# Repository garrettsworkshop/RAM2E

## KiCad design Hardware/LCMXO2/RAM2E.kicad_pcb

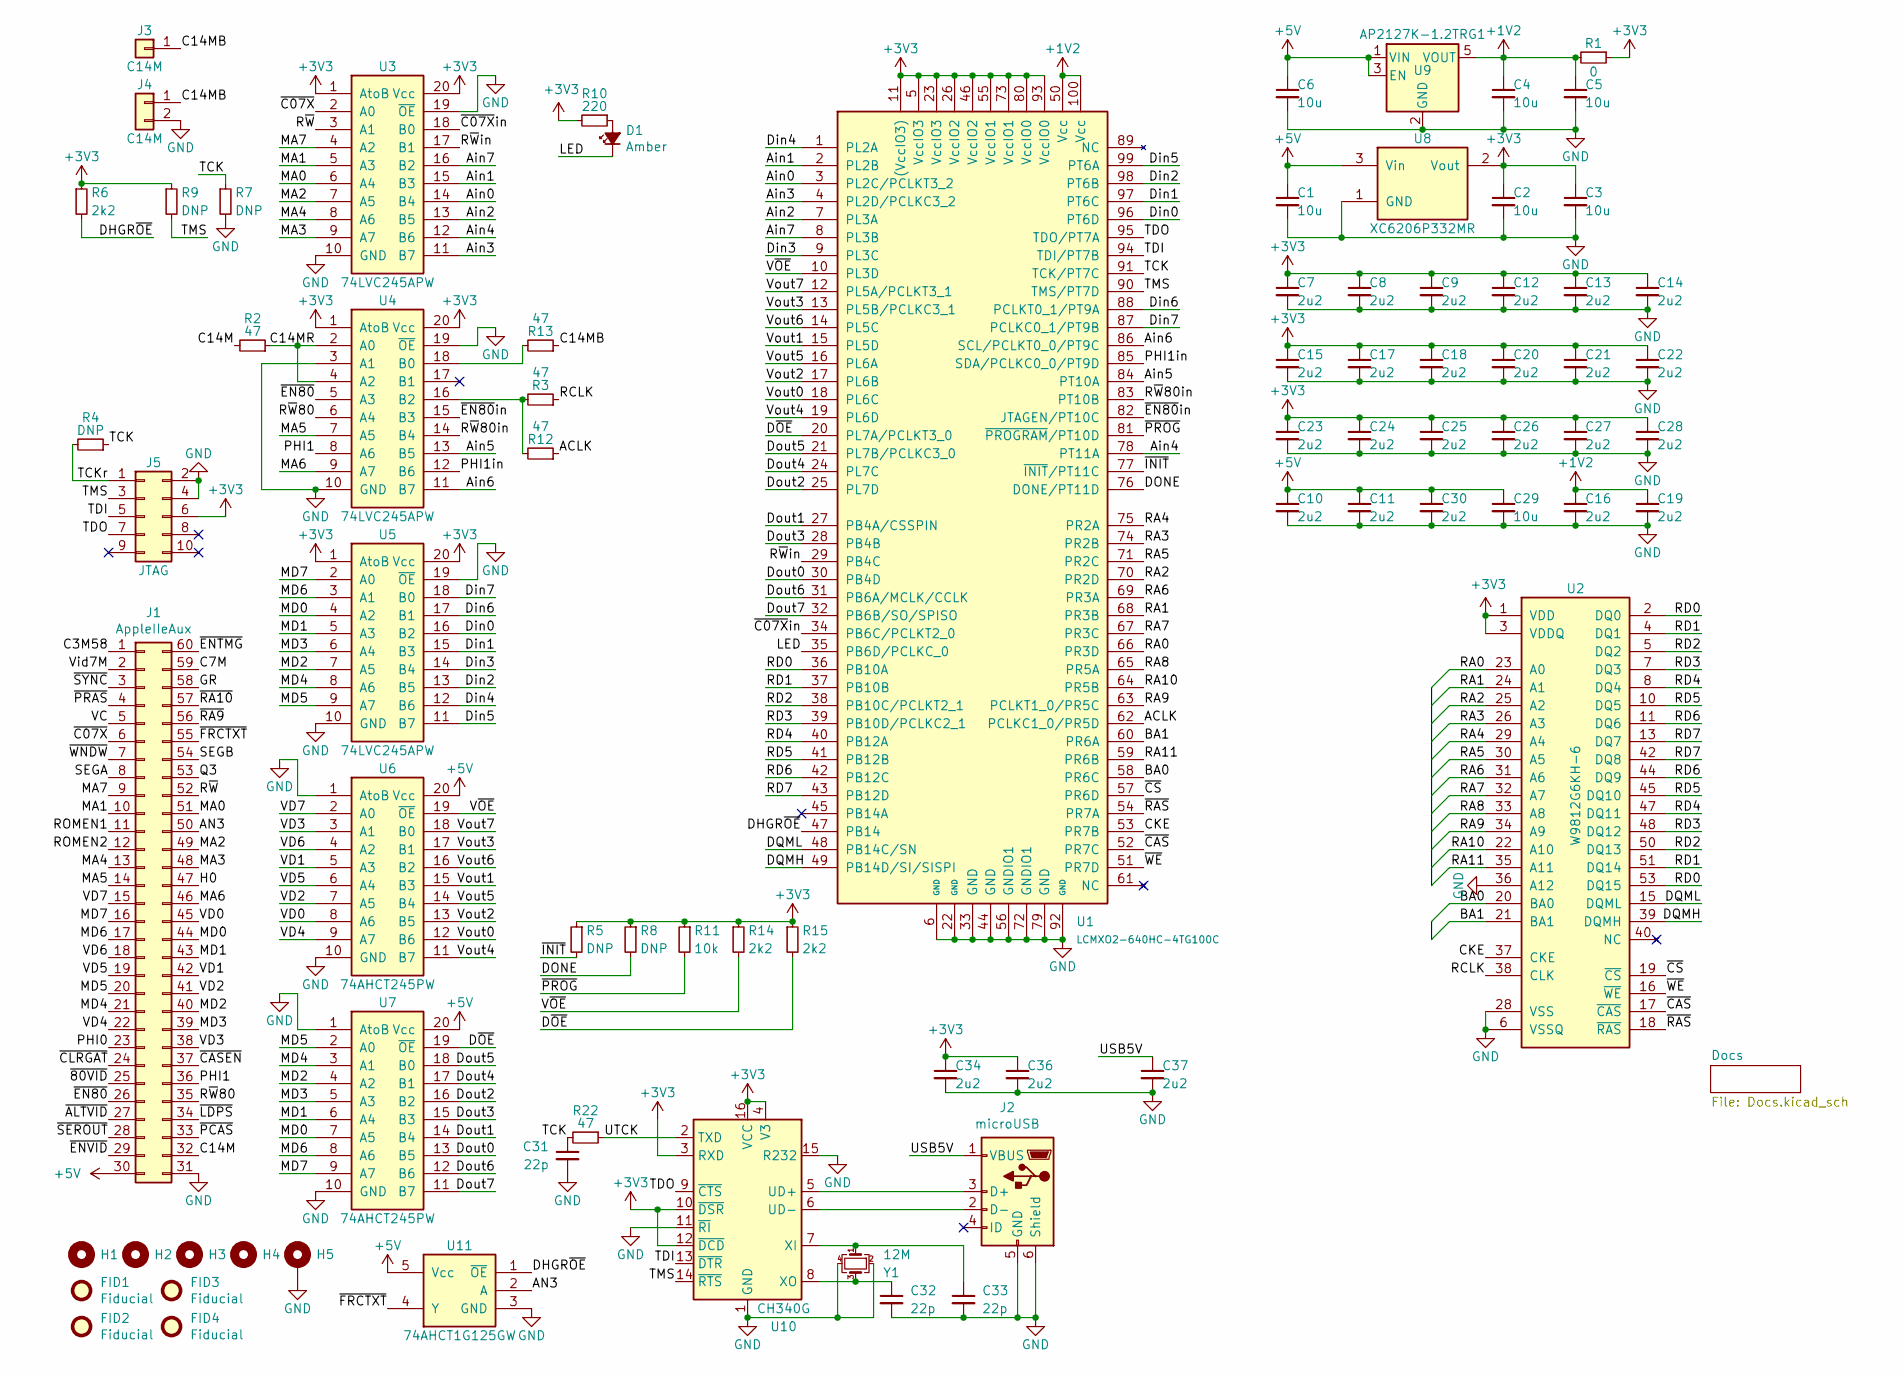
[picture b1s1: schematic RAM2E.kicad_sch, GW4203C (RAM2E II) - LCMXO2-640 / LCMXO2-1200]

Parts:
C1, C2, C3, C4, C5, C6, C29: 10u; C_0805; LCSC Part C15850
C7, C8, C9, C10, C11, C12, C13, C14, C15, C16, C17, C18, C19, C20, C21, C22, C23, C24, C25, C26, C27, C28, C30, C34, C36, C37: 2u2; C_0603; LCSC Part C23630
C31, C32, C33: 22p; C_0603; LCSC Part C1653
D1: Amber; LED_0805; LCSC Part C284932
FID1, FID2, FID3, FID4: Fiducial
H1, H2, H3, H4: PasteHole_1.152mm_NPTH
H5: PasteHole_1.1mm_PTH
J1: AppleIIeAux; AppleIIeAux_Edge
J2: microUSB; USB_Micro-B_Amphenol_10118192-0001; LCSC Part C132564
J3: C14M; EdgeClipHole
J4: C14M; PinHeader_1x02_P2.54mm_Vertical
J5: JTAG; Tag-Connect_TC2050-IDC-FP_2x05_P1.27mm_Vertical
R1: 0; R_0805; LCSC Part C17477
R2, R3, R12, R13, R22: 47; R_0603; LCSC Part C23182
R4, R5, R7, R8, R9: DNP; R_0603
R6, R14, R15: 2k2; R_0603; LCSC Part C4190
R10: 220; R_0805; LCSC Part C17557
R11: 10k; R_0603; LCSC Part C25804
U1: LCMXO2-640HC-4TG100C; TQFP-100_14x14mm_P0.5mm; LCSC Part C1519051
U2: W9812G6KH-6; TSOP-II-54_22.2x10.16mm_P0.8mm; LCSC Part C62379
U3, U4, U5: 74LVC245APW; TSSOP-20_4.4x6.5mm_P0.65mm; LCSC Part C6082
U6, U7: 74AHCT245PW; TSSOP-20_4.4x6.5mm_P0.65mm; LCSC Part C173388
U8: XC6206P332MR; SOT-23; LCSC Part C5446
U9: AP2127K-1.2TRG1; SOT-23-5; LCSC Part C151376
U10: CH340G; SOIC-16_3.9mm; LCSC Part C14267
U11: 74AHCT1G125GW; SOT-353; LCSC Part C12495
Y1: 12M; Crystal_SMD_3225-4Pin_3.2x2.5mm; LCSC Part C9002

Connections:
+1V2: C4.1, C5.1, C16.1, C19.1, R1.2, U1.50 (Vcc), U1.100 (Vcc), U9.5 (VOUT)
+3V3: C2.1, C3.1, C7.1, C8.1, C9.1, C12.1, C13.1, C14.1, C15.1, C17.1, C18.1, C20.1, C21.1, C22.1, C23.1, C24.1, C25.1, C26.1, C27.1, C28.1, C34.1, C36.1, J5.6, R1.1, R5.1, R6.1, R8.1, R9.1, R10.2, R11.1, R14.1, R15.1, U1.5 (VccIO3), U1.11 ((VccIO3)), U1.23 (VccIO3), U1.26 (VccIO2), U1.46 (VccIO2), U1.55 (VccIO1), U1.73 (VccIO1), U1.80 (VccIO0), U1.93 (VccIO0), U2.1 (VDD), U2.3 (VDDQ), U2.9 (VDDQ), U2.14 (VDD), U2.27 (VDD), U2.43 (VDDQ), U2.49 (VDDQ), U3.1 (AtoB), U3.20 (Vcc), U4.1 (AtoB), U4.20 (Vcc), U5.1 (AtoB), U5.20 (Vcc), U8.2 (Vout), U10.3 (RXD), U10.4 (V3), U10.10 (~DSR), U10.12 (~DCD), U10.16 (VCC)
+5V: C1.1, C6.1, C10.1, C11.1, C29.1, C30.1, J1.30, U6.20 (Vcc), U7.20 (Vcc), U8.3 (Vin), U9.1 (VIN), U9.3 (EN), U11.5 (Vcc)
/ACLK: R12.1, U1.62 (PCLKC1_0/PR5D)
/AN3: J1.50, U11.2 (A)
/Ain0: U1.3 (PL2C/PCLKT3_2), U3.14 (B4)
/Ain1: U1.2 (PL2B), U3.15 (B3)
/Ain2: U1.7 (PL3A), U3.13 (B5)
/Ain3: U1.4 (PL2D/PCLKC3_2), U3.11 (B7)
/Ain4: U1.78 (PT11A), U3.12 (B6)
/Ain5: U1.84 (PT10A), U4.13 (B5)
/Ain6: U1.86 (SCL/PCLKT0_0/PT9C), U4.11 (B7)
/Ain7: U1.8 (PL3B), U3.16 (B2)
/BA0: U1.58 (PR6C), U2.20 (BA0)
/BA1: U1.60 (PR6A), U2.21 (BA1)
/C3M58: J1.1
/C7M: J1.59
/C14M: J1.32, R2.2
/C14MB: J3.1, J4.1, R13.1
/C14MR: R2.1, U4.2 (A0), U4.4 (A2)
/CKE: U1.53 (PR7B), U2.37 (CKE)
/DHGR~OE: R6.2, U1.47 (PB14), U11.1 (~OE)
/DONE: R8.2, U1.76 (DONE/PT11D)
/DQMH: U1.49 (PB14D/SI/SISPI), U2.39 (DQMH)
/DQML: U1.48 (PB14C/SN), U2.15 (DQML)
/Din0: U1.96 (PT6D), U5.16 (B2)
/Din1: U1.97 (PT6C), U5.15 (B3)
/Din2: U1.98 (PT6B), U5.13 (B5)
/Din3: U1.9 (PL3C), U5.14 (B4)
/Din4: U1.1 (PL2A), U5.12 (B6)
/Din5: U1.99 (PT6A), U5.11 (B7)
/Din6: U1.88 (PCLKT0_1/PT9A), U5.17 (B1)
/Din7: U1.87 (PCLKC0_1/PT9B), U5.18 (B0)
/Dout0: U1.30 (PB4D), U7.13 (B5)
/Dout1: U1.27 (PB4A/CSSPIN), U7.14 (B4)
/Dout2: U1.25 (PL7D), U7.16 (B2)
/Dout3: U1.28 (PB4B), U7.15 (B3)
/Dout4: U1.24 (PL7C), U7.17 (B1)
/Dout5: U1.21 (PL7B/PCLKC3_0), U7.18 (B0)
/Dout6: U1.31 (PB6A/MCLK/CCLK), U7.12 (B6)
/Dout7: U1.32 (PB6B/SO/SPISO), U7.11 (B7)
/D~OE: R15.2, U1.20 (PL7A/PCLKT3_0), U7.19 (~OE)
/GR: J1.58
/H0: J1.47
/LED: D1.1 (K), U1.35 (PB6D/PCLKC_0)
/MA0: J1.51, U3.6 (A4)
/MA1: J1.10, U3.5 (A3)
/MA2: J1.49, U3.7 (A5)
/MA3: J1.48, U3.9 (A7)
/MA4: J1.13, U3.8 (A6)
/MA5: J1.14, U4.7 (A5)
/MA6: J1.46, U4.9 (A7)
/MA7: J1.9, U3.4 (A2)
/MD0: J1.44, U5.4 (A2), U7.7 (A5)
/MD1: J1.43, U5.5 (A3), U7.6 (A4)
/MD2: J1.40, U5.7 (A5), U7.4 (A2)
/MD3: J1.39, U5.6 (A4), U7.5 (A3)
/MD4: J1.21, U5.8 (A6), U7.3 (A1)
/MD5: J1.20, U5.9 (A7), U7.2 (A0)
/MD6: J1.17, U5.3 (A1), U7.8 (A6)
/MD7: J1.16, U5.2 (A0), U7.9 (A7)
/PHI0: J1.23
/PHI1: J1.36, U4.8 (A6)
/PHI1in: U1.85 (SDA/PCLKC0_0/PT9D), U4.12 (B6)
/Q3: J1.53
/RA0: U1.66 (PR3D), U2.23 (A0)
/RA1: U1.68 (PR3B), U2.24 (A1)
/RA2: U1.70 (PR2D), U2.25 (A2)
/RA3: U1.74 (PR2B), U2.26 (A3)
/RA4: U1.75 (PR2A), U2.29 (A4)
/RA5: U1.71 (PR2C), U2.30 (A5)
/RA6: U1.69 (PR3A), U2.31 (A6)
/RA7: U1.67 (PR3C), U2.32 (A7)
/RA8: U1.65 (PR5A), U2.33 (A8)
/RA9: U1.63 (PCLKT1_0/PR5C), U2.34 (A9)
/RA10: U1.64 (PR5B), U2.22 (A10)
/RA11: U1.59 (PR6B), U2.35 (A11)
/RCLK: R3.1, U2.38 (CLK)
/RD0: U1.36 (PB10A), U2.2 (DQ0), U2.53 (DQ15)
/RD1: U1.37 (PB10B), U2.4 (DQ1), U2.51 (DQ14)
/RD2: U1.38 (PB10C/PCLKT2_1), U2.5 (DQ2), U2.50 (DQ13)
/RD3: U1.39 (PB10D/PCLKC2_1), U2.7 (DQ3), U2.48 (DQ12)
/RD4: U1.40 (PB12A), U2.8 (DQ4), U2.47 (DQ11)
/RD5: U1.41 (PB12B), U2.10 (DQ5), U2.45 (DQ10)
/RD6: U1.42 (PB12C), U2.11 (DQ6), U2.44 (DQ9)
/RD7: U1.43 (PB12D), U2.13 (DQ7), U2.42 (DQ8)
/ROMEN1: J1.11
/ROMEN2: J1.12
/R~W: J1.52, U3.3 (A1)
/R~W80: J1.35, U4.6 (A4)
/R~W80in: U1.83 (PT10B), U4.14 (B4)
/R~Win: U1.29 (PB4C), U3.17 (B1)
/SEGA: J1.8
/SEGB: J1.54
/TCK: C31.1, R4.1, R7.1, R22.2, U1.91 (TCK/PT7C)
/TCKr: J5.1, R4.2
/TDI: J5.5, U1.94 (TDI/PT7B), U10.13 (~DTR)
/TDO: J5.7, U1.95 (TDO/PT7A), U10.9 (~CTS)
/TMS: J5.3, R9.2, U1.90 (TMS/PT7D), U10.14 (~RTS)
/USB5V: C37.1, J2.1 (VBUS)
/UTCK: R22.1, U10.2 (TXD)
/VC: J1.5
/VD0: J1.45, U6.8 (A6)
/VD1: J1.42, U6.5 (A3)
/VD2: J1.41, U6.7 (A5)
/VD3: J1.38, U6.3 (A1)
/VD4: J1.22, U6.9 (A7)
/VD5: J1.19, U6.6 (A4)
/VD6: J1.18, U6.4 (A2)
/VD7: J1.15, U6.2 (A0)
/Vid7M: J1.2
/Vout0: U1.18 (PL6C), U6.12 (B6)
/Vout1: U1.15 (PL5D), U6.15 (B3)
/Vout2: U1.17 (PL6B), U6.13 (B5)
/Vout3: U1.13 (PL5B/PCLKC3_1), U6.17 (B1)
/Vout4: U1.19 (PL6D), U6.11 (B7)
/Vout5: U1.16 (PL6A), U6.14 (B4)
/Vout6: U1.14 (PL5C), U6.16 (B2)
/Vout7: U1.12 (PL5A/PCLKT3_1), U6.18 (B0)
/V~OE: R14.2, U1.10 (PL3D), U6.19 (~OE)
/~80VID: J1.25
/~ALTVID: J1.27
/~C07X: J1.6, U3.2 (A0)
/~C07Xin: U1.34 (PB6C/PCLKT2_0), U3.18 (B0)
/~CASEN: J1.37
/~CAS: U1.52 (PR7C), U2.17 (~CAS)
/~CLRGAT: J1.24
/~CS: U1.57 (PR6D), U2.19 (~CS)
/~EN80: J1.26, U4.5 (A3)
/~EN80in: U1.82 (JTAGEN/PT10C), U4.15 (B3)
/~ENTMG: J1.60
/~ENVID: J1.29
/~FRCTXT: J1.55, U11.4 (Y)
/~INIT: R5.2, U1.77 (~INIT/PT11C)
/~LDPS: J1.34
/~PCAS: J1.33
/~PRAS: J1.4
/~PROG: R11.2, U1.81 (~PROGRAM/PT10D)
/~RA9: J1.56
/~RA10: J1.57
/~RAS: U1.54 (PR7A), U2.18 (~RAS)
/~SEROUT: J1.28
/~SYNC: J1.3
/~WE: U1.51 (PR7D), U2.16 (~WE)
/~WNDW: J1.7
GND: C1.2, C2.2, C3.2, C4.2, C5.2, C6.2, C7.2, C8.2, C9.2, C10.2, C11.2, C12.2, C13.2, C14.2, C15.2, C16.2, C17.2, C18.2, C19.2, C20.2, C21.2, C22.2, C23.2, C24.2, C25.2, C26.2, C27.2, C28.2, C29.2, C30.2, C31.2, C32.2, C33.2, C34.2, C36.2, C37.2, H5.1, J1.31, J2.5 (GND), J2.6 (Shield), J4.2, J5.2, J5.4, R7.2, U1.6 (GND), U1.22 (GND), U1.33 (GND), U1.44 (GND), U1.56 (GNDIO1), U1.72 (GNDIO1), U1.79 (GND), U1.92 (GND), U2.6 (VSSQ), U2.12 (VSSQ), U2.28 (VSS), U2.36 (A12), U2.41 (VSS), U2.46 (VSSQ), U2.52 (VSSQ), U2.54 (VSS), U3.10 (GND), U3.19 (~OE), U4.3 (A1), U4.10 (GND), U4.19 (~OE), U5.10 (GND), U5.19 (~OE), U6.1 (AtoB), U6.10 (GND), U7.1 (AtoB), U7.10 (GND), U8.1 (GND), U9.2 (GND), U10.1 (GND), U10.11 (~RI), U10.15 (R232), U11.3 (GND), Y1.2, Y1.4
unnamed: D1.2 (A), R10.1
unnamed: J2.3 (D+), U10.5 (UD+)
unnamed: J2.2 (D-), U10.6 (UD-)
unnamed: R13.2, U4.18 (B0)
unnamed: R3.2, R12.2, U4.16 (B2)
unnamed: C33.1, U10.7 (XI), Y1.1
unnamed: C32.1, U10.8 (XO), Y1.3

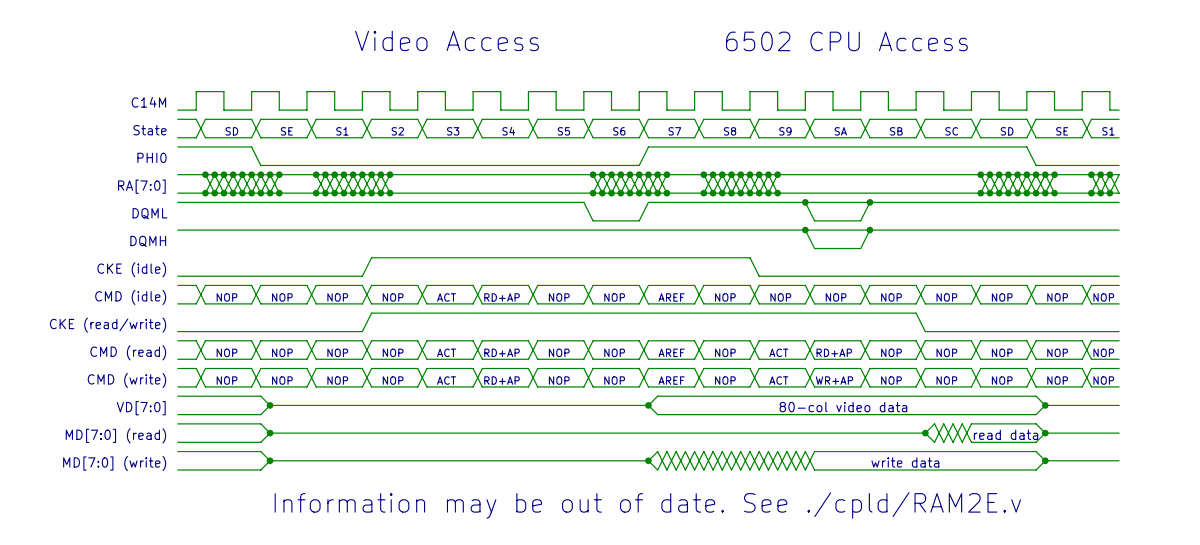
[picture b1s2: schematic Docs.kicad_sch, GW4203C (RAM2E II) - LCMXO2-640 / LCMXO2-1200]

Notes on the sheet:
NOP
Video Access
MD[7:0] (read)
CMD (idle)
MD[7:0] (write)
ACT
DQML
CMD (read)
Information may be out of date. See ./cpld/RAM2E.v
CKE (read/write)
AREF
VD[7:0]
80-col video data
RD+AP
CKE (idle)
State
write data
C14M
6502 CPU Access
DQMH
WR+AP
PHI0
RA[7:0]
read data
CMD (write)

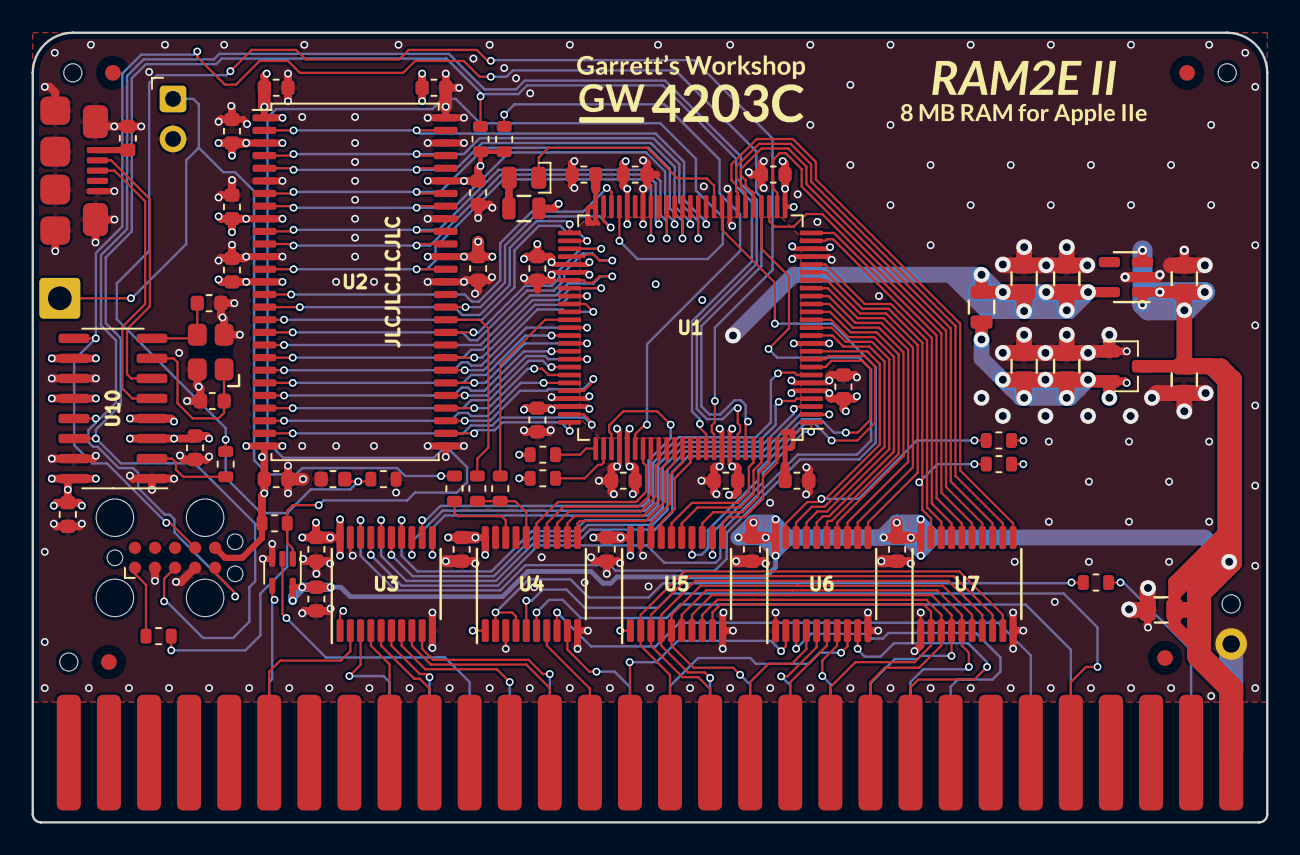
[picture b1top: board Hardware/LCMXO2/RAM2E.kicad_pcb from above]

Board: 4 copper layers, 78.2 x 50.0 mm, 79 parts (0 on the bottom side), 127 nets.

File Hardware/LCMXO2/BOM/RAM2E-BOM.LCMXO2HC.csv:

Reference, Quantity, Value, Footprint, Datasheet, LCSC Part, Mfg. Part Numbers, Notes
C7 C8 C9 C10 C11 C12 C13 C14 C15 C16 C17 C18 C19 C20 C21 C22 C23 C24 C25 C26 C27 C28 C30 ,23,2u2,stdpads:C_0603,,C23630,Samsung CL10A225KO8NNNC,"10V or higher. Any manufacturer's part is acceptable but Samsung, Murata, Yageo preferred."
C1 C2 C3 C4 C5 C6 C29 ,7,10u,stdpads:C_0805,,C15850,Samsung CL21A106KAYNNNE,"10V or higher. Any manufacturer's part is acceptable but Samsung, Murata, Yageo preferred."
C31 ,1,15p,stdpads:C_0603,,C1644,Samsung CL10C150JB8NNNC,"10V or higher. Any manufacturer's part is acceptable but Samsung, Murata, Yageo preferred."
D1 ,1,Amber,stdpads:LED_0805,,C34499,Hubei Kento C34499,Any manufacturer's part is acceptable.
FID1 FID2 FID3 FID4 ,4,Fiducial,stdpads:Fiducial,,,,DNP - SMT vision system fiducial
H1 H2 H3 H4 ,4, ,stdpads:PasteHole_1.152mm_NPTH,,,,DNP - mounting hole for solder paste printing
H5 ,1, ,stdpads:PasteHole_1.1mm_PTH,,,,DNP - mounting hole
J1 ,1,AppleIIeAux,stdpads:AppleIIeAux_Edge,,,,DNP - edge connector
J2 ,1,JTAG,stdpads:TC2050,,,,DNP - test pad connector
J3 ,1,C14M,Connector_PinHeader_2.54mm:PinHeader_1x02_P2.54mm_Vertical,,,,DNP
R1 ,1,0,stdpads:R_0805,,C17477,Uniroyal 0805W8F0000T5E,Any manufacturer's part is acceptable.
R10 ,1,220,stdpads:R_0805,,C17557,Uniroyal 0805W8F2200T5E,Any manufacturer's part is acceptable.
R2 R3 R4 R12 R13 ,5,47,stdpads:R_0603,,C23182,Uniroyal 0603WAF470JT5E,Any manufacturer's part is acceptable.
R6 ,1,0,stdpads:R_0805,,C17477,Uniroyal 0805W8F0000T5E,Any manufacturer's part is acceptable.
R7 ,1,DNP,stdpads:R_0805,,,,
R5 R8 R9 R11 ,4,10k,stdpads:R_0603,,C25804,Uniroyal 0603WAF1002T5E,Any manufacturer's part is acceptable.
U1 ,1,LCMXO2-TG100,stdpads:TQFP-100_14x14mm_P0.5mm,,C1519051,"Lattice LCMXO2-640HC-4TG100C, Lattice LCMXO2-640HC-5TG100C, Lattice LCMXO2-640HC-6TG100C, Lattice LCMXO2-640HC-4TG100I, Lattice LCMXO2-640HC-5TG100I, Lattice LCMXO2-640HC-6TG100I, Lattice LCMXO2-1200HC-4TG100C, Lattice LCMXO2-1200HC-5TG100C, Lattice LCMXO2-1200HC-6TG100C, Lattice LCMXO2-1200HC-4TG100I, Lattice LCMXO2-1200HC-5TG100I, Lattice LCMXO2-1200HC-6TG100I",
U2 ,1,W9812G6KH-6,stdpads:TSOP-II-54_22.2x10.16mm_P0.8mm,,C62379,"Winbond W9812G6KH-6, Winbond W9812G6KH-6I, Winbond W9825G6KH-6, Winbond W9825G6KH-6I, ISSI IS42S16160J-6TL, ISSI IS42S16160J-6TLI, Micron MT48LC16M16A2P-6A :G, Micron MT48LC16M16A2P-6A IT:G",Most 166 MHz 128/256 Mbit x16 SDRAM is acceptable.
U4 ,1,74LVC245APW,stdpads:TSSOP-20_4.4x6.5mm_P0.65mm,,C6082,"NXP 74LVC245APW, TI SN74LVC245APW, NXP 74AHC245PW, NXP 74AHC245APW, TI 74AHC245PW",Most 74LVC245 or 74AHC245 in TSSOP-20 package is acceptable.
U3 U5 ,2,74AHC245PW,stdpads:TSSOP-20_4.4x6.5mm_P0.65mm,,C6082,"NXP 74LVC245APW, TI SN74LVC245APW, NXP 74AHC245PW, NXP 74AHC245APW, TI 74AHC245PW",Most 74LVC245 or 74AHC245 in TSSOP-20 package is acceptable.
U6 U7 ,2,74AHCT245PW,stdpads:TSSOP-20_4.4x6.5mm_P0.65mm,,C173388,"NXP 74AHCT245PW, NXP 74AHCT245APW, TI SN74AHCT245PW",Most 74AHCT245 in TSSOP-20 package is acceptable.
U8 ,1,XC6206P332MR,stdpads:SOT-23,,C5446,Torex XC6206P332MR,Most 3.3V regulator in SOT-23 package is acceptable.
U9 ,1,DNP,stdpads:SOT-23-5,,,,

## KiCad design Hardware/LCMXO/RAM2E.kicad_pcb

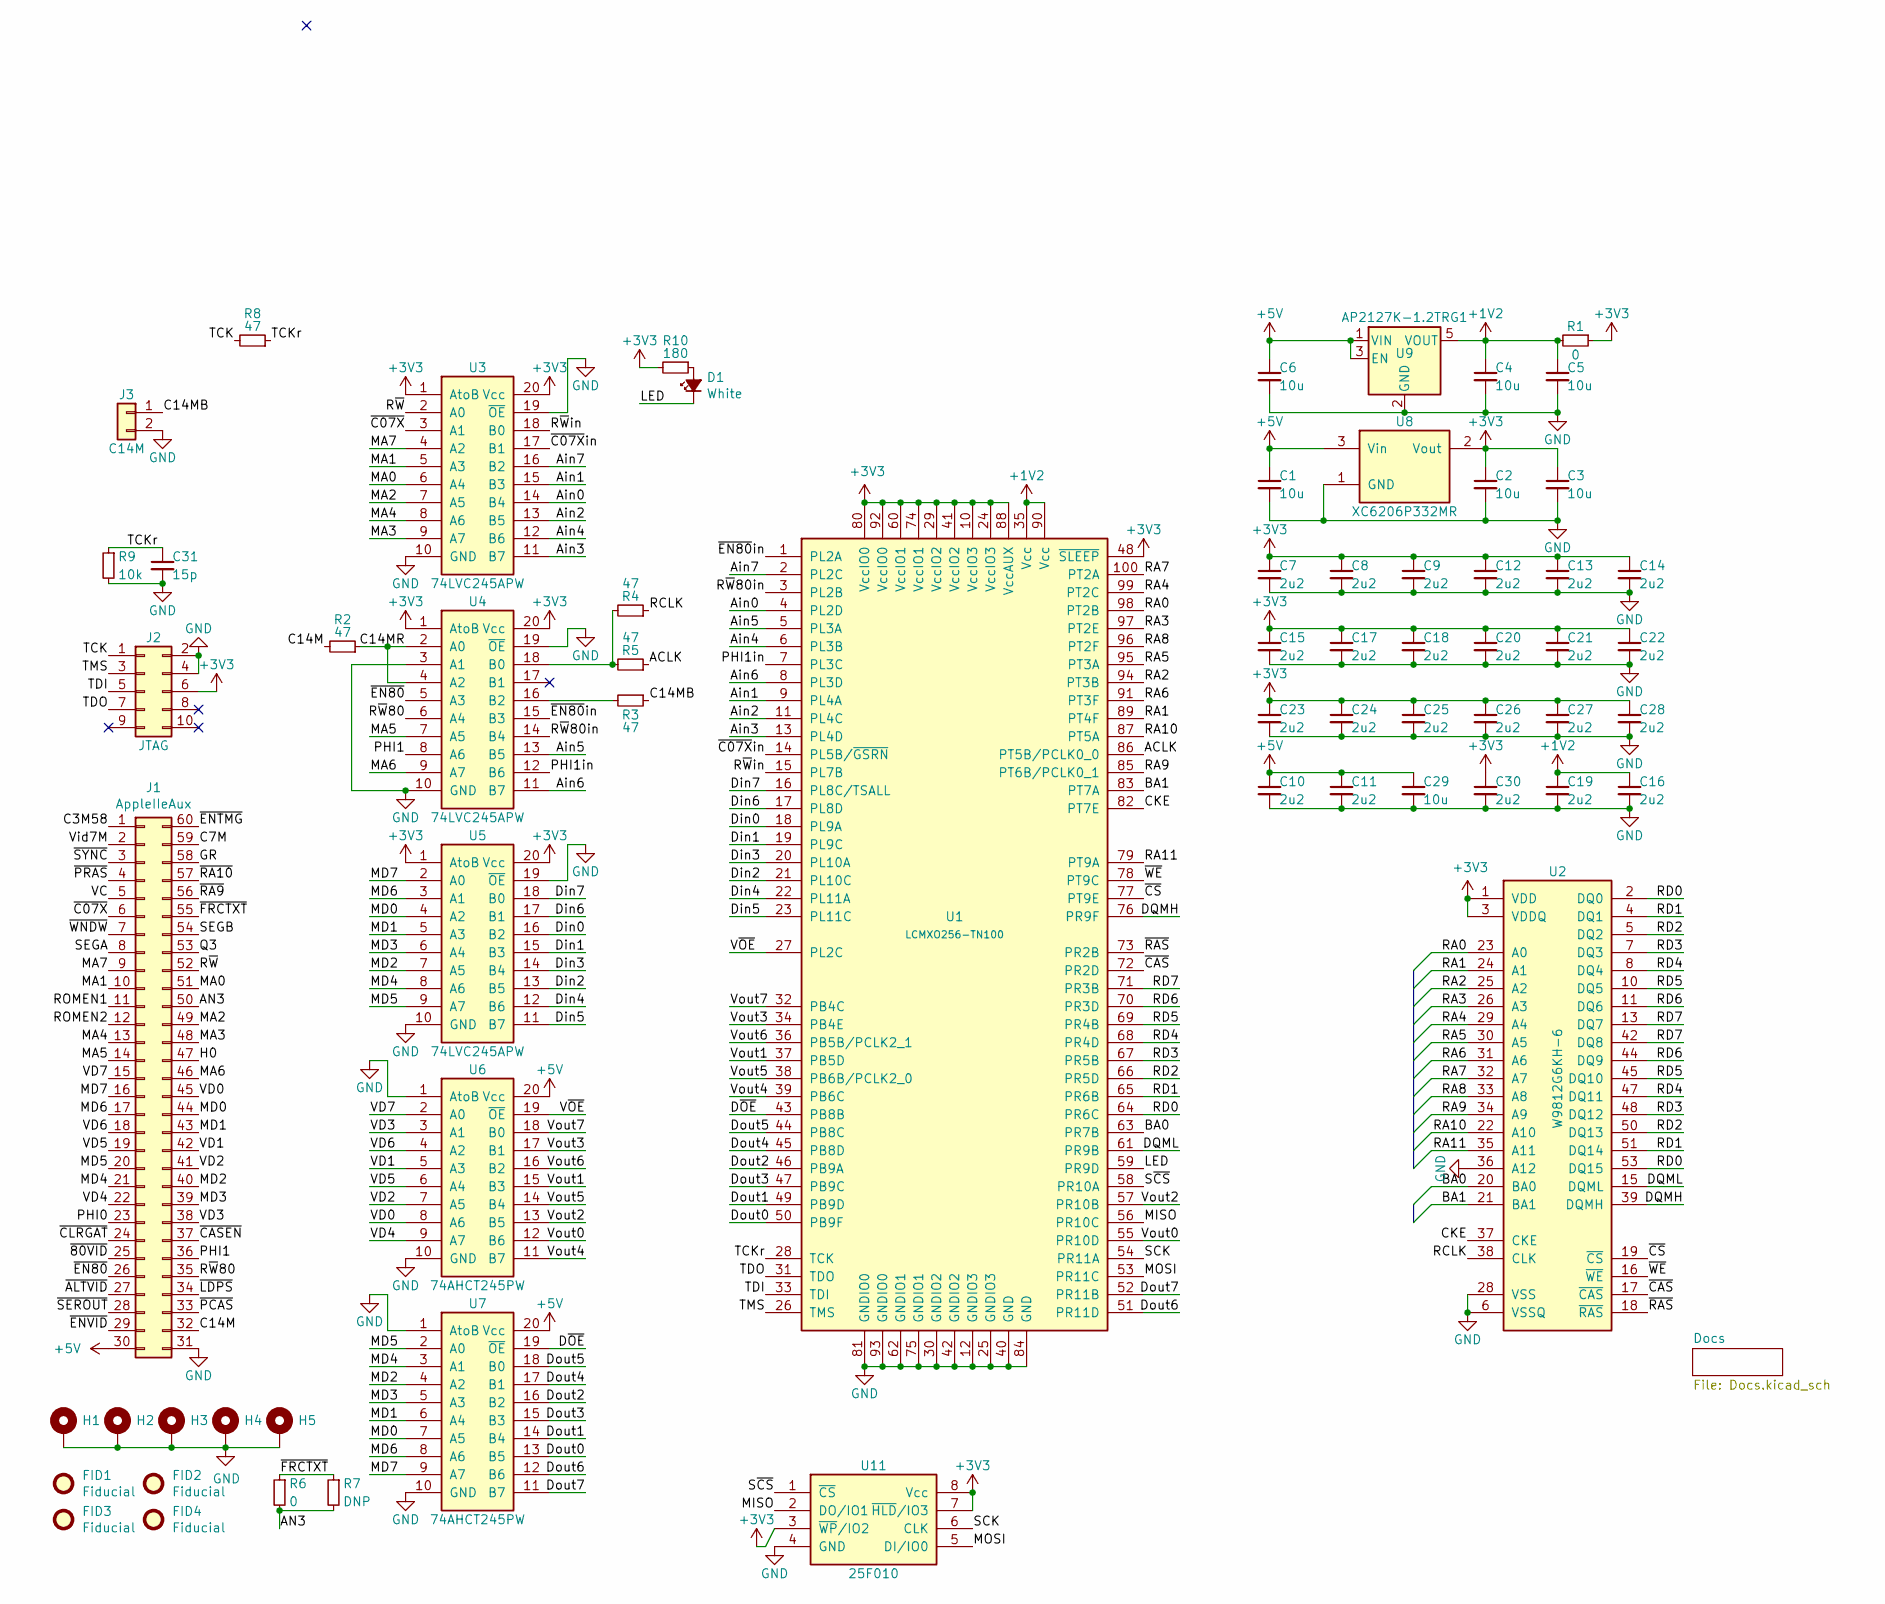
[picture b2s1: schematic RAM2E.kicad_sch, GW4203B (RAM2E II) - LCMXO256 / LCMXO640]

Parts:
C1, C2, C3, C4, C5, C6, C29: 10u; C_0805; Mfg. Part Numbers Samsung CL21A106KAYNNNE; LCSC Part C15850
C7, C8, C9, C10, C11, C12, C13, C14, C15, C16, C17, C18, C19, C20, C21, C22, C23, C24, C25, C26, C27, C28, C30: 2u2; C_0603; Mfg. Part Numbers Samsung CL10A225KO8NNNC; LCSC Part C23630
C31: 15p; C_0603
D1: White; LED_0805; Mfg. Part Numbers Hubei Kento C34499; LCSC Part C34499
FID1, FID2, FID3, FID4: Fiducial
H1, H2, H3, H4: PasteHole_1.152mm_NPTH
H5: PasteHole_1.1mm_PTH
J1: AppleIIeAux; AppleIIeAux_Edge
J2: JTAG; TC2050
J3: C14M; PinHeader_1x02_P2.54mm_Vertical
R1, R6: 0; R_0805; Mfg. Part Numbers Uniroyal 0805W8F0000T5E; LCSC Part C17477
R2, R3, R4, R5, R8: 47; R_0603; Mfg. Part Numbers Uniroyal 0603WAF470JT5E; LCSC Part C23182
R7: DNP; R_0805
R9: 10k; R_0603; Mfg. Part Numbers Uniroyal 0603WAF1002T5E; LCSC Part C25804
R10: 180; R_0805; Mfg. Part Numbers Uniroyal 0805W8F1800T5E; LCSC Part C25270
U1: LCMXO256-TN100; TQFP-100_14x14mm_P0.5mm; Mfg. Part Numbers Lattice LCMXO256C-3TN100C, Lattice LCMX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; LCSC Part C1550734
U2: W9812G6KH-6; TSOP-II-54_22.2x10.16mm_P0.8mm; Mfg. Part Numbers Winbond W9812G6KH-6, Winbond W9812G6KH-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; LCSC Part C62379
U3, U4, U5: 74LVC245APW; TSSOP-20_4.4x6.5mm_P0.65mm; Mfg. Part Numbers NXP 74LVC245APW, TI SN74LVC245APW, NXP 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; LCSC Part C6082
U6, U7: 74AHCT245PW; TSSOP-20_4.4x6.5mm_P0.65mm; Mfg. Part Numbers NXP 74AHCT245PW, NXP 74AHCT245APW, TI S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; LCSC Part C173388
U8: XC6206P332MR; SOT-23; Mfg. Part Numbers Torex XC6206P332MR; LCSC Part C5446
U9: AP2127K-1.2TRG1; SOT-23-5; Mfg. Part Numbers Diodes AP2127K-1.2TRG1, Torex XC6228D12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; LCSC Part C151376
U11: 25F010; SOIC-8_5.3mm; Mfg. Part Numbers Zetta ZD25WD20BTIGT, Adesto AT25SF081-S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; LCSC Part C2687406

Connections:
+1V2: C4.1, C5.1, C16.1, C19.1, R1.2, U1.35 (Vcc), U1.90 (Vcc), U9.5 (VOUT)
+3V3: C2.1, C3.1, C7.1, C8.1, C9.1, C12.1, C13.1, C14.1, C15.1, C17.1, C18.1, C20.1, C21.1, C22.1, C23.1, C24.1, C25.1, C26.1, C27.1, C28.1, C30.1, J2.6, R1.1, R10.2, U1.10 (VccIO3), U1.24 (VccIO3), U1.29 (VccIO2), U1.41 (VccIO2), U1.48 (~SLEEP), U1.60 (VccIO1), U1.74 (VccIO1), U1.80 (VccIO0), U1.88 (VccAUX), U1.92 (VccIO0), U2.1 (VDD), U2.3 (VDDQ), U2.9 (VDDQ), U2.14 (VDD), U2.27 (VDD), U2.43 (VDDQ), U2.49 (VDDQ), U3.1 (AtoB), U3.20 (Vcc), U4.1 (AtoB), U4.20 (Vcc), U5.1 (AtoB), U5.20 (Vcc), U8.2 (Vout), U11.3 (~WP/IO2), U11.7 (~HLD/IO3), U11.8 (Vcc)
+5V: C1.1, C6.1, C10.1, C11.1, C29.1, J1.30, U6.20 (Vcc), U7.20 (Vcc), U8.3 (Vin), U9.1 (VIN), U9.3 (EN)
/ACLK: R5.1, U1.86 (PT5B/PCLK0_0)
/AN3: J1.50, R6.2, R7.2
/Ain0: U1.4 (PL2D), U3.14 (B4)
/Ain1: U1.9 (PL4A), U3.15 (B3)
/Ain2: U1.11 (PL4C), U3.13 (B5)
/Ain3: U1.13 (PL4D), U3.11 (B7)
/Ain4: U1.6 (PL3B), U3.12 (B6)
/Ain5: U1.5 (PL3A), U4.13 (B5)
/Ain6: U1.8 (PL3D), U4.11 (B7)
/Ain7: U1.2 (PL2C), U3.16 (B2)
/BA0: U1.63 (PR7B), U2.20 (BA0)
/BA1: U1.83 (PT7A), U2.21 (BA1)
/C3M58: J1.1
/C7M: J1.59
/C14M: J1.32, R2.2
/C14MB: J3.1, R3.1
/C14MR: R2.1, U4.2 (A0), U4.4 (A2)
/CKE: U1.82 (PT7E), U2.37 (CKE)
/DQMH: U1.76 (PR9F), U2.39 (DQMH)
/DQML: U1.61 (PR9B), U2.15 (DQML)
/Din0: U1.18 (PL9A), U5.16 (B2)
/Din1: U1.19 (PL9C), U5.15 (B3)
/Din2: U1.21 (PL10C), U5.13 (B5)
/Din3: U1.20 (PL10A), U5.14 (B4)
/Din4: U1.22 (PL11A), U5.12 (B6)
/Din5: U1.23 (PL11C), U5.11 (B7)
/Din6: U1.17 (PL8D), U5.17 (B1)
/Din7: U1.16 (PL8C/TSALL), U5.18 (B0)
/Dout0: U1.50 (PB9F), U7.13 (B5)
/Dout1: U1.49 (PB9D), U7.14 (B4)
/Dout2: U1.46 (PB9A), U7.16 (B2)
/Dout3: U1.47 (PB9C), U7.15 (B3)
/Dout4: U1.45 (PB8D), U7.17 (B1)
/Dout5: U1.44 (PB8C), U7.18 (B0)
/Dout6: U1.51 (PR11D), U7.12 (B6)
/Dout7: U1.52 (PR11B), U7.11 (B7)
/D~OE: U1.43 (PB8B), U7.19 (~OE)
/GR: J1.58
/H0: J1.47
/LED: D1.1 (K), U1.59 (PR9D)
/MA0: J1.51, U3.6 (A4)
/MA1: J1.10, U3.5 (A3)
/MA2: J1.49, U3.7 (A5)
/MA3: J1.48, U3.9 (A7)
/MA4: J1.13, U3.8 (A6)
/MA5: J1.14, U4.7 (A5)
/MA6: J1.46, U4.9 (A7)
/MA7: J1.9, U3.4 (A2)
/MD0: J1.44, U5.4 (A2), U7.7 (A5)
/MD1: J1.43, U5.5 (A3), U7.6 (A4)
/MD2: J1.40, U5.7 (A5), U7.4 (A2)
/MD3: J1.39, U5.6 (A4), U7.5 (A3)
/MD4: J1.21, U5.8 (A6), U7.3 (A1)
/MD5: J1.20, U5.9 (A7), U7.2 (A0)
/MD6: J1.17, U5.3 (A1), U7.8 (A6)
/MD7: J1.16, U5.2 (A0), U7.9 (A7)
/MISO: U1.56 (PR10C), U11.2 (DO/IO1)
/MOSI: U1.53 (PR11C), U11.5 (DI/IO0)
/PHI0: J1.23
/PHI1: J1.36, U4.8 (A6)
/PHI1in: U1.7 (PL3C), U4.12 (B6)
/Q3: J1.53
/RA0: U1.98 (PT2B), U2.23 (A0)
/RA1: U1.89 (PT4F), U2.24 (A1)
/RA2: U1.94 (PT3B), U2.25 (A2)
/RA3: U1.97 (PT2E), U2.26 (A3)
/RA4: U1.99 (PT2C), U2.29 (A4)
/RA5: U1.95 (PT3A), U2.30 (A5)
/RA6: U1.91 (PT3F), U2.31 (A6)
/RA7: U1.100 (PT2A), U2.32 (A7)
/RA8: U1.96 (PT2F), U2.33 (A8)
/RA9: U1.85 (PT6B/PCLK0_1), U2.34 (A9)
/RA10: U1.87 (PT5A), U2.22 (A10)
/RA11: U1.79 (PT9A), U2.35 (A11)
/RCLK: R4.1, U2.38 (CLK)
/RD0: U1.64 (PR6C), U2.2 (DQ0), U2.53 (DQ15)
/RD1: U1.65 (PR6B), U2.4 (DQ1), U2.51 (DQ14)
/RD2: U1.66 (PR5D), U2.5 (DQ2), U2.50 (DQ13)
/RD3: U1.67 (PR5B), U2.7 (DQ3), U2.48 (DQ12)
/RD4: U1.68 (PR4D), U2.8 (DQ4), U2.47 (DQ11)
/RD5: U1.69 (PR4B), U2.10 (DQ5), U2.45 (DQ10)
/RD6: U1.70 (PR3D), U2.11 (DQ6), U2.44 (DQ9)
/RD7: U1.71 (PR3B), U2.13 (DQ7), U2.42 (DQ8)
/ROMEN1: J1.11
/ROMEN2: J1.12
/R~W: J1.52, U3.2 (A0)
/R~W80: J1.35, U4.6 (A4)
/R~W80in: U1.3 (PL2B), U4.14 (B4)
/R~Win: U1.15 (PL7B), U3.18 (B0)
/SCK: U1.54 (PR11A), U11.6 (CLK)
/SEGA: J1.8
/SEGB: J1.54
/S~CS: U1.58 (PR10A), U11.1 (~CS)
/TCK: J2.1, R8.2
/TCKr: C31.1, R8.1, R9.1, U1.28 (TCK)
/TDI: J2.5, U1.33 (TDI)
/TDO: J2.7, U1.31 (TDO)
/TMS: J2.3, U1.26 (TMS)
/VC: J1.5
/VD0: J1.45, U6.8 (A6)
/VD1: J1.42, U6.5 (A3)
/VD2: J1.41, U6.7 (A5)
/VD3: J1.38, U6.3 (A1)
/VD4: J1.22, U6.9 (A7)
/VD5: J1.19, U6.6 (A4)
/VD6: J1.18, U6.4 (A2)
/VD7: J1.15, U6.2 (A0)
/Vid7M: J1.2
/Vout0: U1.55 (PR10D), U6.12 (B6)
/Vout1: U1.37 (PB5D), U6.15 (B3)
/Vout2: U1.57 (PR10B), U6.13 (B5)
/Vout3: U1.34 (PB4E), U6.17 (B1)
/Vout4: U1.39 (PB6C), U6.11 (B7)
/Vout5: U1.38 (PB6B/PCLK2_0), U6.14 (B4)
/Vout6: U1.36 (PB5B/PCLK2_1), U6.16 (B2)
/Vout7: U1.32 (PB4C), U6.18 (B0)
/V~OE: U1.27 (PL2C), U6.19 (~OE)
/~80VID: J1.25
/~ALTVID: J1.27
/~C07X: J1.6, U3.3 (A1)
/~C07Xin: U1.14 (PL5B/~GSRN), U3.17 (B1)
/~CASEN: J1.37
/~CAS: U1.72 (PR2D), U2.17 (~CAS)
/~CLRGAT: J1.24
/~CS: U1.77 (PT9E), U2.19 (~CS)
/~EN80: J1.26, U4.5 (A3)
/~EN80in: U1.1 (PL2A), U4.15 (B3)
/~ENTMG: J1.60
/~ENVID: J1.29
/~FRCTXT: J1.55, R6.1, R7.1
/~LDPS: J1.34
/~PCAS: J1.33
/~PRAS: J1.4
/~RA9: J1.56
/~RA10: J1.57
/~RAS: U1.73 (PR2B), U2.18 (~RAS)
/~SEROUT: J1.28
/~SYNC: J1.3
/~WE: U1.78 (PT9C), U2.16 (~WE)
/~WNDW: J1.7
GND: C1.2, C2.2, C3.2, C4.2, C5.2, C6.2, C7.2, C8.2, C9.2, C10.2, C11.2, C12.2, C13.2, C14.2, C15.2, C16.2, C17.2, C18.2, C19.2, C20.2, C21.2, C22.2, C23.2, C24.2, C25.2, C26.2, C27.2, C28.2, C29.2, C30.2, C31.2, H1.1, H2.1, H3.1, H4.1, H5.1, J1.31, J2.2, J2.4, J3.2, R9.2, U1.12 (GNDIO3), U1.25 (GNDIO3), U1.30 (GNDIO2), U1.40 (GND), U1.42 (GNDIO2), U1.62 (GNDIO1), U1.75 (GNDIO1), U1.81 (GNDIO0), U1.84 (GND), U1.93 (GNDIO0), U2.6 (VSSQ), U2.12 (VSSQ), U2.28 (VSS), U2.36 (A12), U2.41 (VSS), U2.46 (VSSQ), U2.52 (VSSQ), U2.54 (VSS), U3.10 (GND), U3.19 (~OE), U4.3 (A1), U4.10 (GND), U4.19 (~OE), U5.10 (GND), U5.19 (~OE), U6.1 (AtoB), U6.10 (GND), U7.1 (AtoB), U7.10 (GND), U8.1 (GND), U9.2 (GND), U11.4 (GND)
unnamed: D1.2 (A), R10.1
unnamed: R4.2, R5.2, U4.18 (B0)
unnamed: R3.2, U4.16 (B2)

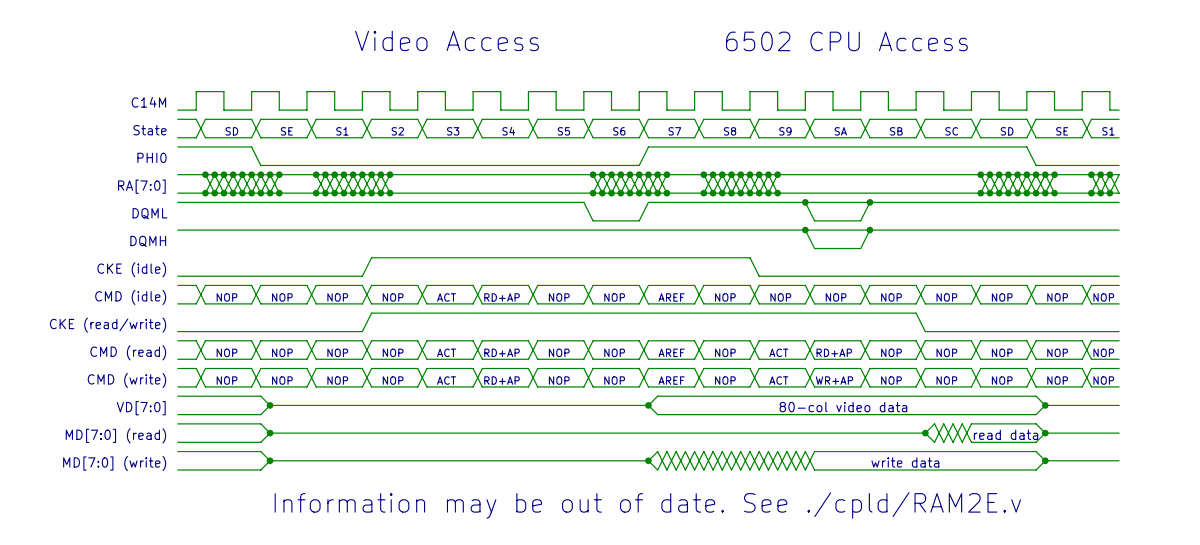
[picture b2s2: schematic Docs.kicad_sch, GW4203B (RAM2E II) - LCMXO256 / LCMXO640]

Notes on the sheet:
VD[7:0]
NOP
State
CKE (read/write)
AREF
CMD (read)
6502 CPU Access
RD+AP
Information may be out of date. See ./cpld/RAM2E.v
ACT
CMD (idle)
PHI0
C14M
CMD (write)
Video Access
CKE (idle)
DQMH
80-col video data
MD[7:0] (read)
write data
MD[7:0] (write)
RA[7:0]
DQML
read data
WR+AP

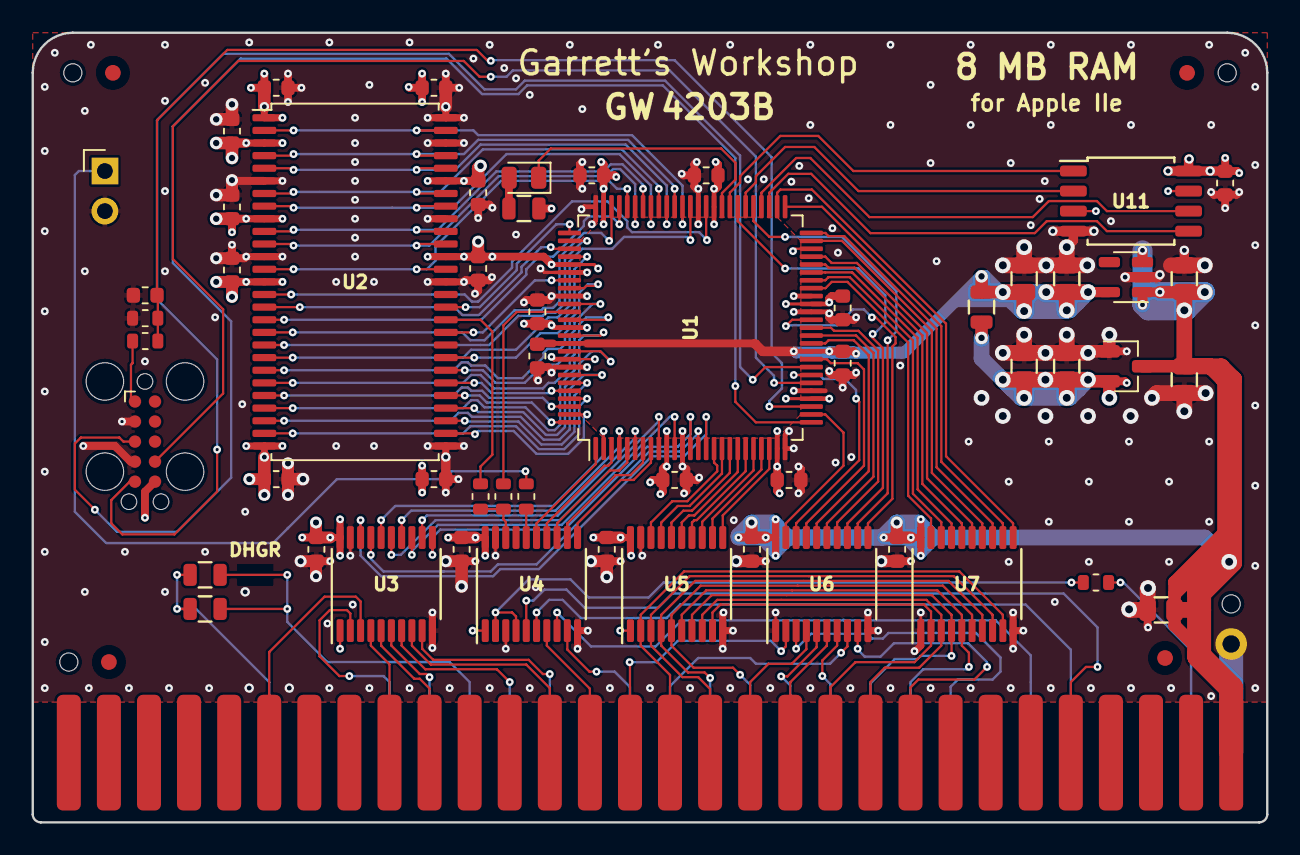
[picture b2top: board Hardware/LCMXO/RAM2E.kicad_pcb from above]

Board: 4 copper layers, 78.2 x 50.0 mm, 64 parts (0 on the bottom side), 121 nets.

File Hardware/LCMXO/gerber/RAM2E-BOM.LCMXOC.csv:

Reference, Quantity, Value, Footprint, Datasheet, LCSC Part, Mfg. Part Numbers, Notes
C7 C8 C9 C10 C11 C12 C13 C14 C15 C16 C17 C18 C19 C20 C21 C22 C23 C24 C25 C26 C27 C28 C30 ,23,2u2,stdpads:C_0603,,C23630,Samsung CL10A225KO8NNNC,"10V or higher. Any manufacturer's part is acceptable but Samsung, Murata, Yageo preferred."
C1 C2 C3 C4 C5 C6 C29 ,7,10u,stdpads:C_0805,,C15850,Samsung CL21A106KAYNNNE,"10V or higher. Any manufacturer's part is acceptable but Samsung, Murata, Yageo preferred."
C31 ,1,15p,stdpads:C_0603,,,,"10V or higher. Any manufacturer's part is acceptable but Samsung, Murata, Yageo preferred."
D1 ,1,White,stdpads:LED_0805,,C34499,Hubei Kento C34499,Any manufacturer's part is acceptable.
FID1 FID2 FID3 FID4 ,4,Fiducial,stdpads:Fiducial,,,,DNP - SMT vision system fiducial
H1 H2 H3 H4 ,4, ,stdpads:PasteHole_1.152mm_NPTH,,,,DNP - mounting hole for solder paste printing
H5 ,1, ,stdpads:PasteHole_1.1mm_PTH,,,,DNP - mounting hole
J1 ,1,AppleIIeAux,stdpads:AppleIIeAux_Edge,,,,DNP - edge connector
J2 ,1,JTAG,stdpads:TC2050,,,,DNP - test pad connector
J3 ,1,C14M,Connector_PinHeader_2.54mm:PinHeader_1x02_P2.54mm_Vertical,,,,DNP
R1 ,1,0,stdpads:R_0805,,C17477,Uniroyal 0805W8F0000T5E,Any manufacturer's part is acceptable.
R10 ,1,180,stdpads:R_0805,,C25270,Uniroyal 0805W8F1800T5E,Any manufacturer's part is acceptable.
R2 R3 R4 R5 R8 ,5,47,stdpads:R_0603,,C23182,Uniroyal 0603WAF470JT5E,Any manufacturer's part is acceptable.
R6 ,1,0,stdpads:R_0805,,C17477,Uniroyal 0805W8F0000T5E,Any manufacturer's part is acceptable.
R7 ,1,DNP,stdpads:R_0805,,,,
R9 ,1,10k,stdpads:R_0603,,C25804,Uniroyal 0603WAF1002T5E,Any manufacturer's part is acceptable.
U1 ,1,LCMXO256-TN100,stdpads:TQFP-100_14x14mm_P0.5mm,,C1550734,"Lattice LCMXO256C-3TN100C, Lattice LCMXO256C-4TN100C, Lattice LCMXO256C-5TN100C, Lattice LCMXO256C-3TN100I, Lattice LCMXO256C-4TN100I, Lattice LCMXO640C-3TN100C, Lattice LCMXO640C-4TN100C, Lattice LCMXO640C-5TN100C, Lattice LCMXO640C-3TN100I, Lattice LCMXO640C-4TN100I",
U11 ,1,25F010,stdpads:SOIC-8_5.3mm,,C2687406,"Zetta ZD25WD20BTIGT, Adesto AT25SF081-SSHD, Winbond W25X20CLSNIG",Most SPI flash in SOIC-8 (3.9mm / 150 mil width) package is acceptable.
U2 ,1,W9812G6KH-6,stdpads:TSOP-II-54_22.2x10.16mm_P0.8mm,,C62379,"Winbond W9812G6KH-6, Winbond W9812G6KH-6I, Winbond W9825G6KH-6, Winbond W9825G6KH-6I, ISSI IS42S16160J-6TL, ISSI IS42S16160J-6TLI, Micron MT48LC16M16A2P-6A :G, Micron MT48LC16M16A2P-6A IT:G",Most 166 MHz 128/256 Mbit x16 SDRAM is acceptable.
U3 U4 U5 ,3,74LVC245APW,stdpads:TSSOP-20_4.4x6.5mm_P0.65mm,,C6082,"NXP 74LVC245APW, TI SN74LVC245APW, NXP 74AHC245PW, NXP 74AHC245APW, TI SN74AHC245PW",Most 74LVC245 or 74AHC245 in TSSOP-20 package is acceptable.
U6 U7 ,2,74AHCT245PW,stdpads:TSSOP-20_4.4x6.5mm_P0.65mm,,C173388,"NXP 74AHCT245PW, NXP 74AHCT245APW, TI SN74AHCT245PW",Most 74AHCT245 in TSSOP-20 package is acceptable.
U8 ,1,XC6206P332MR,stdpads:SOT-23,,C5446,Torex XC6206P332MR,Most 3.3V regulator in SOT-23 package is acceptable.
U9 ,1,,stdpads:SOT-23-5,,,,

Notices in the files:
cpld/RAM2E.qsf:
Copyright (C) 1991-2013 Altera Corporation
